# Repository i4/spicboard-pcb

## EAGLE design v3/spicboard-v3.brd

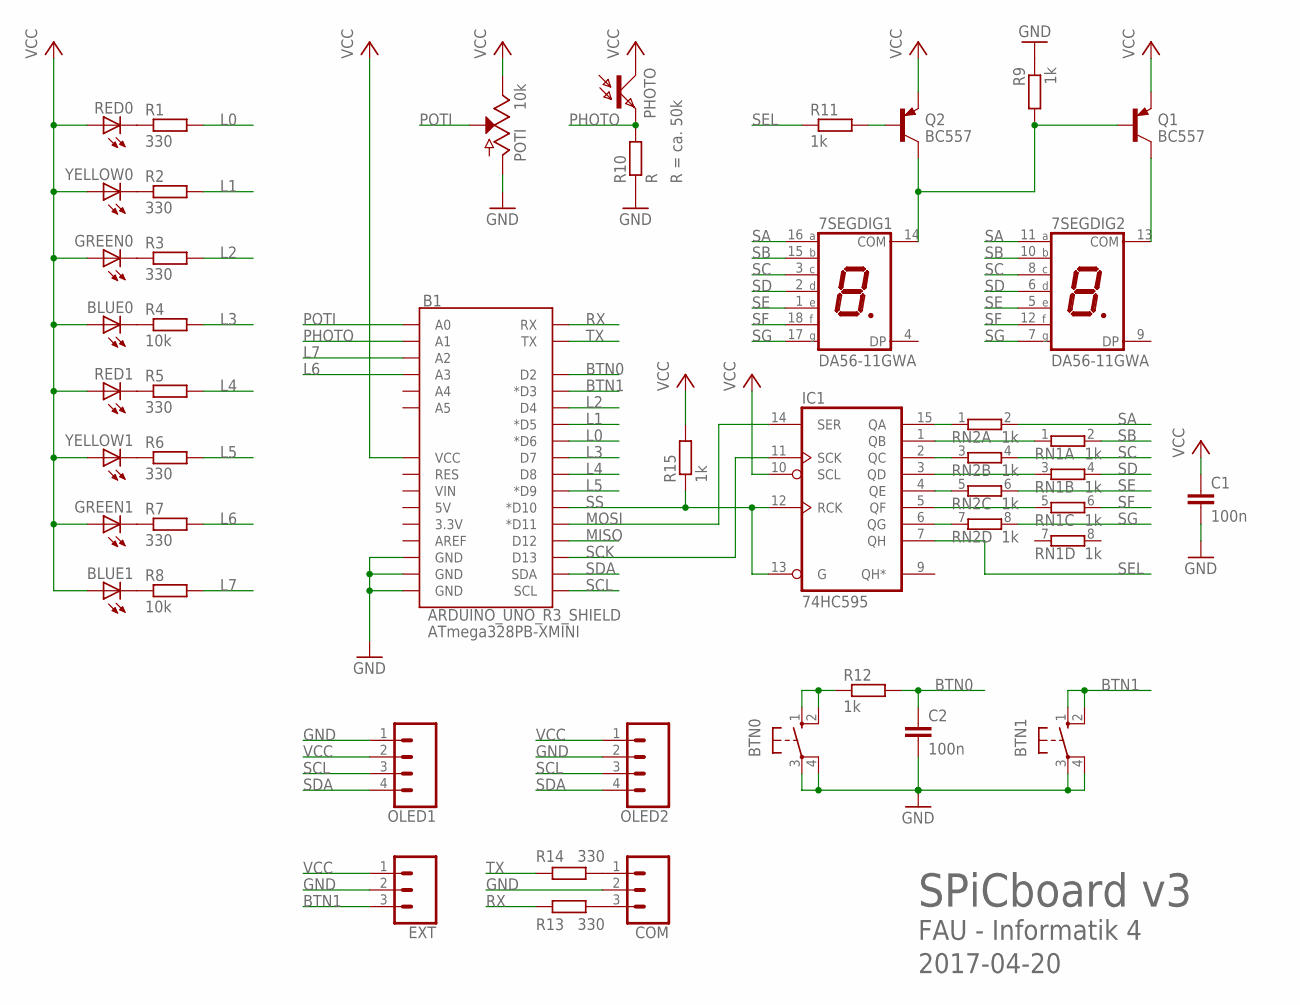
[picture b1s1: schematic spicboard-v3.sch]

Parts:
7SEG: DA56-11GWA; DA56
B1: ARDUINO_UNO_R3_SHIELD; UNO_R3_SHIELD_FINAL
BLUE0, BLUE1: LED5MM
BTN0, BTN1: 10-XX; B3F-10XX
C1, C2: 100n; C2.5-2
COM: CONN_03; 1X03
EXT: CONN_03; 1X03
GREEN0, GREEN1: LED5MM
IC1: 74HC595; DIL16
OLED1, OLED2: CONN_04; 1X04
PHOTO: PTPT; PT
POTI: 10k; POT-PTH-ALPS
Q1, Q2: BC557; TO92-EBC
R1, R2, R3, R5, R6, R7, R13, R14: 330; 0207/10
R4, R8: 10k; 0207/10
R9, R11, R12, R15: 1k; 0207/10
R10: R; 0207/10
RED0, RED1: LED5MM
RN1, RN2: 1k; SIL8
YELLOW0, YELLOW1: LED5MM

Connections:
BTN0: B1.D2, C2.1, R12.2
BTN1: B1.D3 (*D3), BTN1.1 (S), BTN1.2 (S1), EXT.3
GND: B1.GND@0 (GND), B1.GND@1 (GND), B1.GND@2 (GND), BTN0.3, BTN0.4 (P1), BTN1.3, BTN1.4 (P1), C1.2, C2.2, COM.2, EXT.2, IC1.8 (GND), OLED1.1, OLED2.2, POTI.P$3 (A), R9.1, R10.1
L0: B1.D6 (*D6), R1.2
L1: B1.D5 (*D5), R2.2
L2: B1.D4, R3.2
L3: B1.D7, R4.2
L4: B1.D8, R5.2
L5: B1.D9 (*D9), R6.2
L6: B1.A3, R7.2
L7: B1.A2, R8.2
MISO: B1.D12
MOSI: B1.D11 (*D11), IC1.14 (SER)
unnamed: IC1.15 (QA), RN2.1
unnamed: R1.1, RED0.K (C)
unnamed: R2.1, YELLOW0.K (C)
unnamed: GREEN0.K (C), R3.1
unnamed: BLUE0.K (C), R4.1
unnamed: R5.1, RED1.K (C)
unnamed: R6.1, YELLOW1.K (C)
unnamed: GREEN1.K (C), R7.1
unnamed: BLUE1.K (C), R8.1
unnamed: IC1.2 (QC), RN2.3 (1)
unnamed: IC1.4 (QE), RN2.5 (1)
unnamed: IC1.6 (QG), RN2.7 (1)
unnamed: IC1.3 (QD), RN1.3 (1)
unnamed: IC1.1 (QB), RN1.1
unnamed: COM.1, R14.2
unnamed: IC1.5 (QF), RN1.5 (1)
unnamed: 7SEG.13 (COM), Q1.C
unnamed: 7SEG.14 (COM), Q1.B, Q2.C, R9.2
unnamed: BTN0.1 (S), BTN0.2 (S1), R12.1
unnamed: Q2.B, R11.2
unnamed: COM.3, R13.2
PHOTO: B1.A1, PHOTO.E, R10.2
POTI: B1.A0, POTI.P$2 (S)
RX: B1.RX, R13.1
SA: 7SEG.11 (A), 7SEG.16 (A), RN2.2
SB: 7SEG.10 (B), 7SEG.15 (B), RN1.2
SC: 7SEG.3 (C), 7SEG.8 (C), RN2.4 (2)
SCK: B1.D13, IC1.11 (SCK)
SCL: B1.SCL, OLED1.3, OLED2.3
SD: 7SEG.2 (D), 7SEG.6 (D), RN1.4 (2)
SDA: B1.SDA, OLED1.4, OLED2.4
SE: 7SEG.1 (E), 7SEG.5 (E), RN2.6 (2)
SEL: IC1.7 (QH), R11.1
SF: 7SEG.12 (F), 7SEG.18 (F), RN1.6 (2)
SG: 7SEG.7 (G), 7SEG.17 (G), RN2.8 (2)
SS: B1.D10 (*D10), IC1.12 (RCK), IC1.13 (G), R15.1
TX: B1.TX, R14.1
VCC: B1.VCC, BLUE0.A, BLUE1.A, C1.1, EXT.1, GREEN0.A, GREEN1.A, IC1.10 (SCL), IC1.16 (VCC), OLED1.2, OLED2.1, PHOTO.C, POTI.P$1 (E), Q1.E, Q2.E, R15.2, RED0.A, RED1.A, YELLOW0.A, YELLOW1.A

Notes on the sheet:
ATmega328PB-XMINI
R = ca. 50k
SPiCboard v3
FAU - Informatik 4
2017-04-20

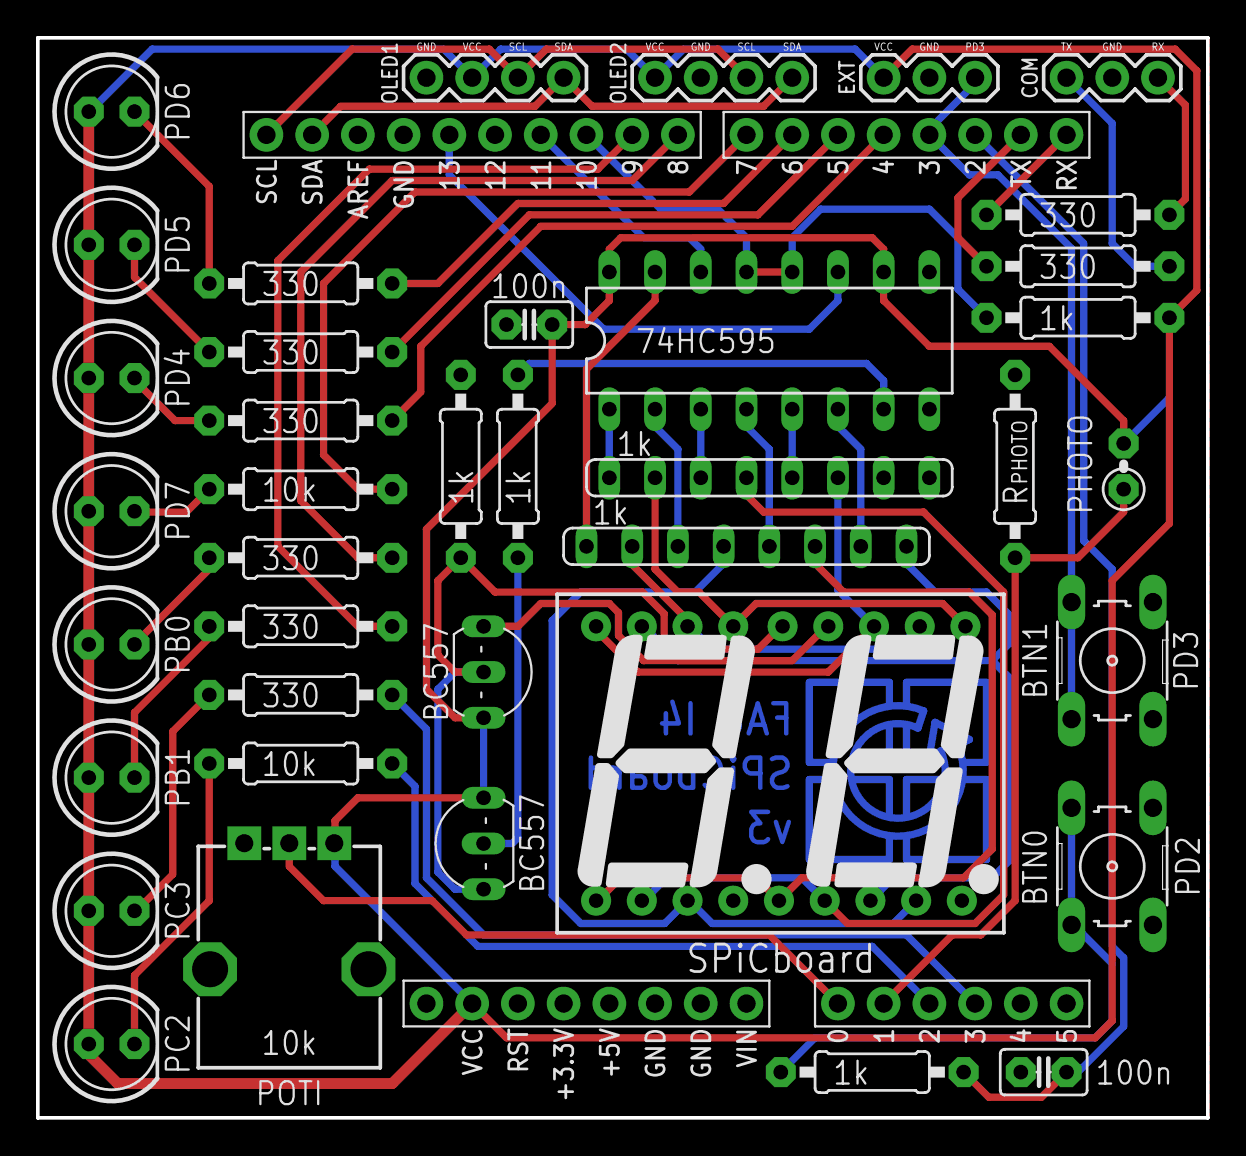
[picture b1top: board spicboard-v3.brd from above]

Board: 2 copper layers, 65.0 x 60.0 mm, 40 parts (0 on the bottom side), 50 nets.

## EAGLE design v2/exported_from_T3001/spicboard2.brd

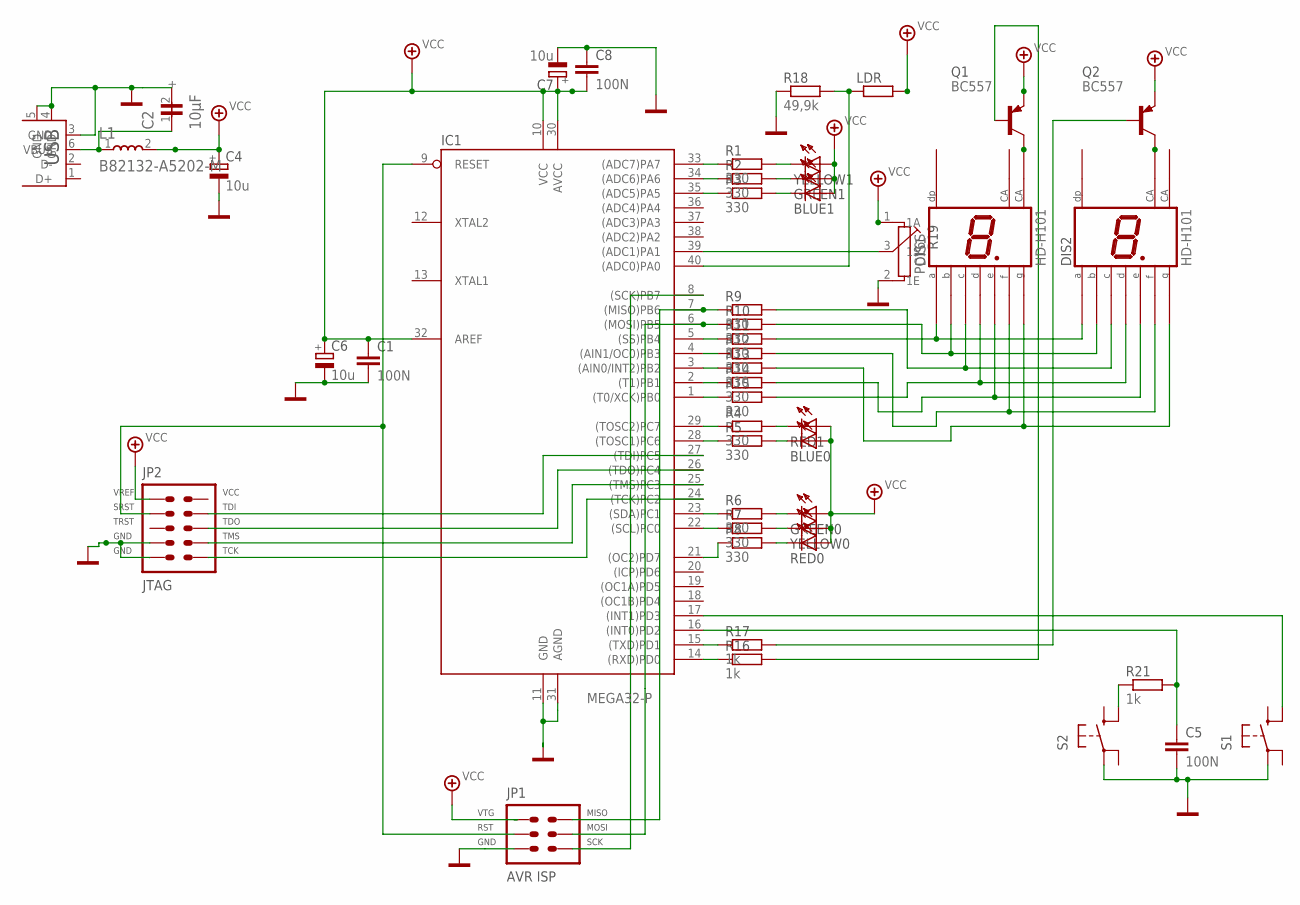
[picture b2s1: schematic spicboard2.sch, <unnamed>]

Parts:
BLUE0: #; #_0
BLUE1: #; #_1
C1: 100N; #_2
C2: 10µF; D6R2,54_ELKO_66
C4: 10u; #_3
C5: 100N; #_4
C6: 10u; #_5
C7: 10u; #_6
C8: 100N; #_7
DIS1: HD-H101; #_8
DIS2: HD-H101; #_9
GREEN0: #; #_10
GREEN1: #; #_11
IC1: MEGA32-P; #_12
JP1: AVR-ISP-6; #_13
JP2: AVR-JTAG-10; #_14
L1: B82132-A5202-M; 6X19R22,86_61
LDR0: #; #_15
Q1: BC557; #_16
Q2: BC557; #_17
R1: 330; #_18
R2: 330; #_19
R3: 330; #_20
R4: 330; #_21
R5: 330; #_22
R6: 330; #_23
R7: 330; #_24
R8: 330; #_25
R9: 330; #_26
R10: 330; #_27
R11: 330; #_28
R12: 330; #_29
R13: 330; #_30
R14: 330; #_31
R15: 330; #_32
R16: 1k; #_33
R17: 1k; #_34
R18: 49,9k; #_35
R19: PC16S; #_36
R21: 1k; #_37
RED0: #; #_38
RED1: #; #_39
S1: #; #_40
S2: #; #_41
USB1: USB-B-H; #_42
YELLOW0: #; #_43
YELLOW1: #; #_44

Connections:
(INT0)PD2: R21.1, S2.2
GND: C1.2, C2.2 (-), C4.2, C5.2, C6.2, C7.2, C8.1, IC1.11 (GND), IC1.31 (AGND), JP1.6, JP2.2, JP2.10, R18.1, R19.2 (1E), S1.3, S2.3, USB1.3 (GND), USB1.4 (GND), USB1.5 (GND)
unnamed: IC1.40 ((ADC0)PA0), LDR0.1, R18.2
unnamed: R1.2, YELLOW1.2
unnamed: GREEN1.2, R2.2
unnamed: BLUE1.2, R3.2
unnamed: R4.2, RED1.2
unnamed: BLUE0.2, R5.2
unnamed: GREEN0.2, R6.2
unnamed: R7.2, YELLOW0.2
unnamed: R8.2, RED0.2
unnamed: IC1.7 ((MISO)PB6), JP1.1, R9.1
unnamed: IC1.6 ((MOSI)PB5), JP1.4, R10.1
unnamed: IC1.5 ((SS)PB4), R11.1
unnamed: IC1.4 ((AIN1/OC0)PB3), R12.1
unnamed: IC1.3 ((AIN0/INT2)PB2), R13.1
unnamed: IC1.2 ((T1)PB1), R14.1
unnamed: IC1.1 ((T0/XCK)PB0), R15.1
unnamed: IC1.33 ((ADC7)PA7), R1.1
unnamed: IC1.34 ((ADC6)PA6), R2.1
unnamed: IC1.35 ((ADC5)PA5), R3.1
unnamed: IC1.29 ((TOSC2)PC7), R4.1
unnamed: IC1.28 ((TOSC1)PC6), R5.1
unnamed: IC1.27 ((TDI)PC5), JP2.9
unnamed: IC1.26 ((TDO)PC4), JP2.3
unnamed: IC1.25 ((TMS)PC3), JP2.5
unnamed: DIS1.7, DIS2.7, R11.2
unnamed: DIS1.6, DIS2.6, R10.2
unnamed: DIS1.4, DIS2.4, R9.2
unnamed: DIS1.2, DIS2.2, R15.2
unnamed: DIS1.1, DIS2.1, R14.2
unnamed: IC1.24 ((TCK)PC2), JP2.1
unnamed: DIS1.10, DIS2.10, R13.2
unnamed: IC1.14 ((RXD)PD0), R16.1
unnamed: IC1.15 ((TXD)PD1), R17.1
unnamed: Q1.1, R16.2
unnamed: Q2.1, R17.2
unnamed: IC1.21 ((OC2)PD7), R8.1
unnamed: IC1.17 ((INT1)PD3), S1.2
unnamed: IC1.39 ((ADC1)PA1), R19.3 (1S)
unnamed: DIS1.9, DIS2.9, R12.2
unnamed: IC1.8 ((SCK)PB7), JP1.3
unnamed: C5.1, IC1.16 ((INT0)PD2), R21.2
unnamed: IC1.9 (RESET), JP1.5, JP2.6
unnamed: IC1.22 ((SCL)PC0), R7.1
unnamed: IC1.23 ((SDA)PC1), R6.1
Sig$47: DIS1.3, Q1.2
Sig$48: DIS2.8, Q2.2
VBUS: C2.1 (+), L1.1, USB1.6 (VBUS)
VCC: BLUE0.1, BLUE1.1, C1.1, C4.1, C6.1, C7.1, C8.2, GREEN0.1, GREEN1.1, IC1.10 (VCC), IC1.30 (AVCC), IC1.32 (AREF), JP1.2, JP2.4, L1.2, LDR0.2, Q1.3, Q2.3, R19.1 (1A), RED0.1, RED1.1, YELLOW0.1, YELLOW1.1

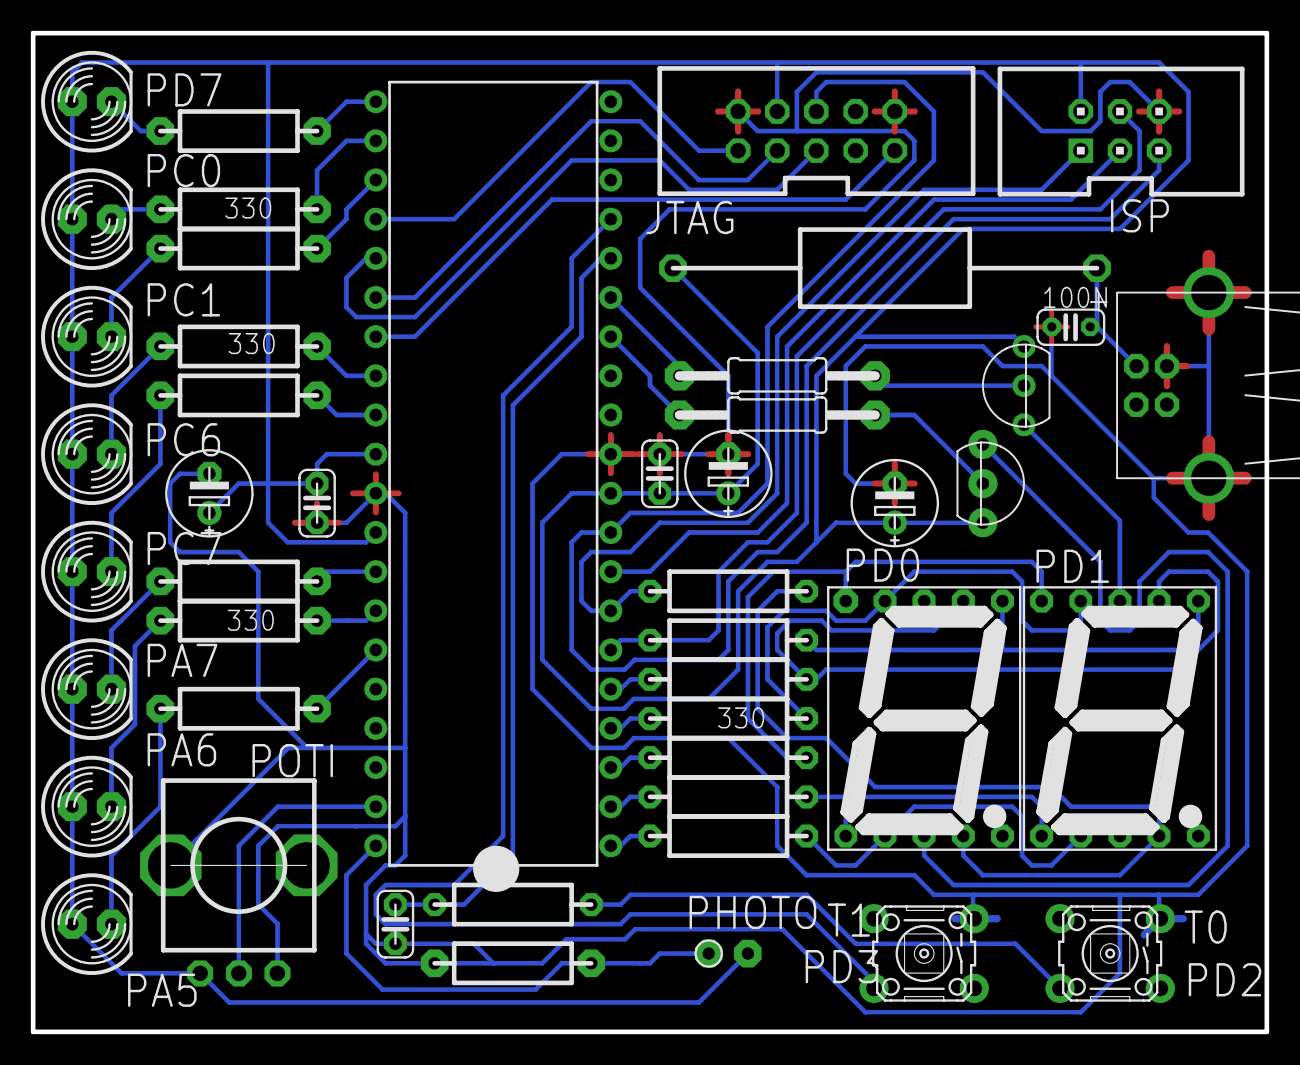
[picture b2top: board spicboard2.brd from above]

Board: 2 copper layers, 80.0 x 64.8 mm, 47 parts (0 on the bottom side), 50 nets.

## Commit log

2013-05-06 Spicboard in uebungen
2016-04-19 Dateien entsprechend der SPiCboard-Version einsortiert
2016-04-21 Exports von T3001 im Eagle-Format
2017-01-13 Beginn der Arbei an Version 3
2017-01-13 Zwischenstand mit (fast) allen Komponenten
2017-01-16 SPiCboard v3 ...
2017-01-16 SPiC Board EXT/COM + TODOs
2017-01-17 TODO
2017-01-17 LEDs ausgerichtet
2017-01-17 Komponenten angeordnet Schieberegister angeschlossen
2017-01-17 7seg leicht verschoben
2017-01-17 Zwischenstand LEDs
2017-01-17 Routing Zwischenstand
2017-01-17 Routing komplett
2017-01-18 Kleinere Korrekturen, ADC fertig
2017-01-18 EXTIRQ auf BTN1, Werte für Widerstandsnetzwerke
2017-01-18 OLED1 ausgetauscht
2017-01-18 Überflüssigen Via gelöscht
2017-01-18 OLED/EXT/COM ausgetauscht
2017-01-18 Labels für LEDs
2017-01-18 Kleinere Traces verschoben
2017-01-18 TODOs nach Erledigung entfernt
2017-01-18 SPiCboard TODOs
2017-01-19 LED labels überprüft
2017-01-19 SPiCboard: i4logo
2017-01-19 SPiCboard: i4logo, LDR -> PHOTO, TODOs aktualisiert
2017-01-19 SPiCboard: Markierung am Widerstandsnetzwerk entfernt
2017-01-19 SPiCboard: Beschriftung verschoben
2017-01-19 SPiCboard: Kleine Änderungen
2017-01-19 SPiCboard: GND plane
2017-01-20 SPiCboard: Design rule 45 Grad Winkel aktiviert
2017-01-20 SPiCboard: SPiCboard v3 -> SPiCboard; Leiterbahnen verschoben
2017-01-23 SPiCboard: IOREF als VCC (anstelle von +5V)
2017-01-23 SPiCboard: TODOs aktualisiert
2017-01-23 SPiCboard: VCC Leitungen verlegt
2017-01-24 SPiCboard: Eagle v8, Multi-CB design rules, Vias entfernt, TODOs aktualisiert
2017-01-24 SPiCboard: Eagle v8
2017-01-24 TODO: Schriften
2017-01-24 Schieberegister mit Pull-Up-Widerstand
2017-01-24 Beschriftung POTI
2017-01-24 Beschriftungen Kondensator
2017-01-24 Beschriftung unten auf Kupfer verschoben
2017-01-24 Beschriftung (auf tNames)
2017-01-24 Beschriftungen (Layer)
2017-01-24 Beschriftungen (nochmal)
2017-01-24 Beschriftungen (Größe)
2017-01-24 Sichtbarkeit der Layer
2017-01-24 IOREF nach VCC umbenannt
2017-01-24 Alle TODOs erledigt
2017-01-25 SPiCboard: 10K -> 10k
2017-02-03 LED Pin geaendert
2017-02-03 PADs in Library angepasst
2017-02-03 7seg DA56 importiert
2017-02-03 SPiCboard: Bauteile ersetzt (PAD-Größe)
2017-02-03 SPiCboard: Leitungen verschoben
2017-02-03 SPiCboard: Bauteile aus Standard-Bibliotheken
2017-02-03 Revert Library Import 7seg DA56
2017-02-03 SPiCboard...
2017-02-03 SPiCboard: PADs fertig
2017-02-03 SPiCboard v3 ueberarbeitet
2017-02-03 SPiCboard: MISO + TODOs
2017-02-06 SPiCboard: 49.9k -> 30k, TODOs entfernt
2017-02-13 SPiCboard: Leitung unter Buttons zentriert
2017-03-20 SPiCboard v3: Photowiderstand durch Phototransistor ersetzt
2017-03-27 Phototransistor 5mm
2017-03-27 SPiCboard: Kleiner Phototransistor, 7-Seg 1k Ohm
2017-03-27 Phototransistor 49.9k
2017-03-27 Phototransistor 100k
2017-04-06 Photowiderstand
2017-04-06 Beschriftung
2017-04-11 SPiCboard: MISO Leitung entfernt
2017-04-20 SPiCboard Schematic
2017-04-20 SPiCboard Schematic uC Pins
2017-05-03 SPiCboard layout v1 & v2 -> archived
2019-04-17 v2 branch
2019-04-17 v1 branch

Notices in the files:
parts and their libraries:
SparkFun-Connectors: Licensing: Creative Commons ShareAlike 4.0 International - https://creativecommons.org/licenses/by-sa/4.0
